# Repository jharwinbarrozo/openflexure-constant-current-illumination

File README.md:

# OpenFlexure Constant Current Illumination

A constant current illumination board for the [Openflexure Microscope](https://openflexure.org/projects/microscope/).

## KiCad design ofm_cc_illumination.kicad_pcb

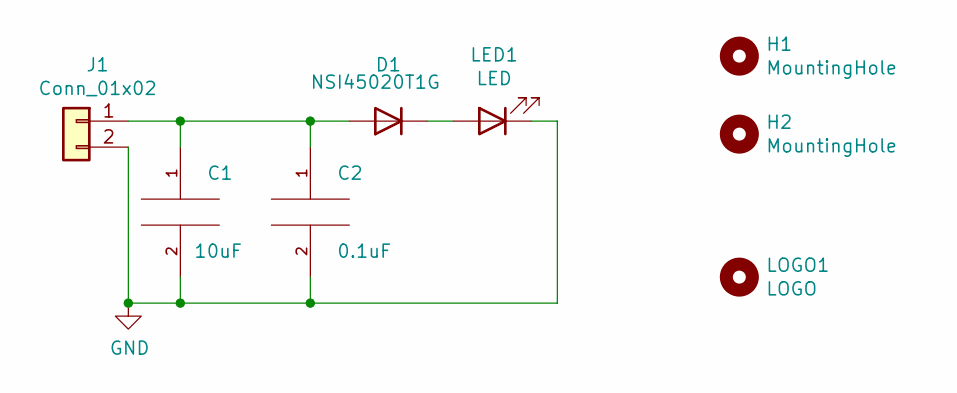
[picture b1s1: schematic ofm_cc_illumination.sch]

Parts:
C1: 10uF; C_0805_2012Metric_Pad1.18x1.45mm_HandSolder; LCSC C342745
C2: 0.1uF; C_0603_1608Metric_Pad1.08x0.95mm_HandSolder; LCSC C282519
D1: NSI45020T1G; SOD3716X135N; LCSC C129159
H1, H2: MountingHole; MountingHole_2.2mm_M2
J1: Conn_01x02; PinHeader_1x02_P2.54mm_Horizontal
LED1: LED; Luxeon_3535L; JLCPCB_CORRECTION 0.4;0;180
LOGO1: LOGO; OFM

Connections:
GND: C1.2, C2.2, J1.2, LED1.1 (K)
unnamed: C1.1, C2.1, D1.2 (A), J1.1
unnamed: D1.1 (K), LED1.2 (A)

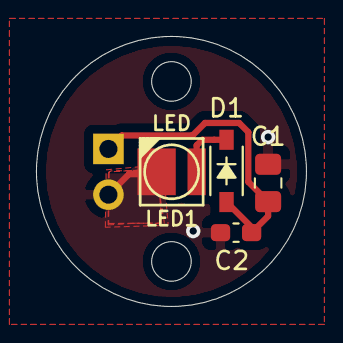
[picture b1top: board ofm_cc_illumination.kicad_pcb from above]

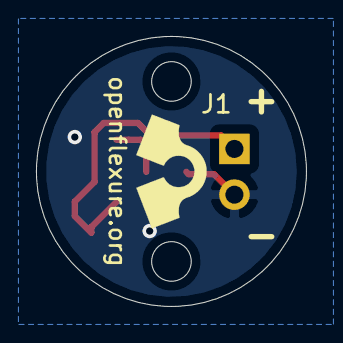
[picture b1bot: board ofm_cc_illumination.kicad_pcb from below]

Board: 2 copper layers, 15.0 x 15.0 mm, 8 parts (4 on the bottom side), 3 nets.

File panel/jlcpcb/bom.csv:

Comment,Designator,Footprint,LCSC,Qty
Conn_01x02,J1,Connector_PinHeader_2.54mm:PinHeader_1x02_P2.54mm_Horizontal,,1
0.1uF,C2,Capacitor_SMD:C_0603_1608Metric_Pad1.08x0.95mm_HandSolder,C282519,1
NSI45020T1G,D1,Custom:SOD3716X135N,C129159,1
10uF,C1,Capacitor_SMD:C_0805_2012Metric_Pad1.18x1.45mm_HandSolder,C342745,1
